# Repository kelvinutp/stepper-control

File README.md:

# stepper controls

This repository will contain the file for controlling stepper motors using a Raspberry pi GPIO and TB6560 drivers

|program|function|
|---|---|
|[clk_signal.py](https://github.com/kelvinutp/stepper-control/blob/main/clock_signal.py)|Generates a constant frequency clock signal (square wave)|
|[only_motors_control.py](https://github.com/kelvinutp/stepper-control/blob/main/only_motors_control.py)|Allows for controlling individual Enable (start/stop) and Direction (changes direction) pin on driver|
|[auto_moving.py](https://github.com/kelvinutp/stepper-control/blob/main/auto_moving.py)|Makes a motor moves repeteadly in prestablished timed sequences|
|[variador.py](https://github.com/kelvinutp/stepper-control/blob/main/variaddor.py)|enables the stepmotor for a soft start and a soft stop by gradually increasing and decreaseing th efrequency|
|[class.py](https://github.com/kelvinutp/stepper-control/blob/main/class.py)|A programmed class that provides all the functionalities for controlling a stepmotor|
|[Django files](https://github.com/kelvinutp/stepper-control/tree/main/django%20files)|a Django project created for providing a sort of UI capable of doing almost everything that is done by code|

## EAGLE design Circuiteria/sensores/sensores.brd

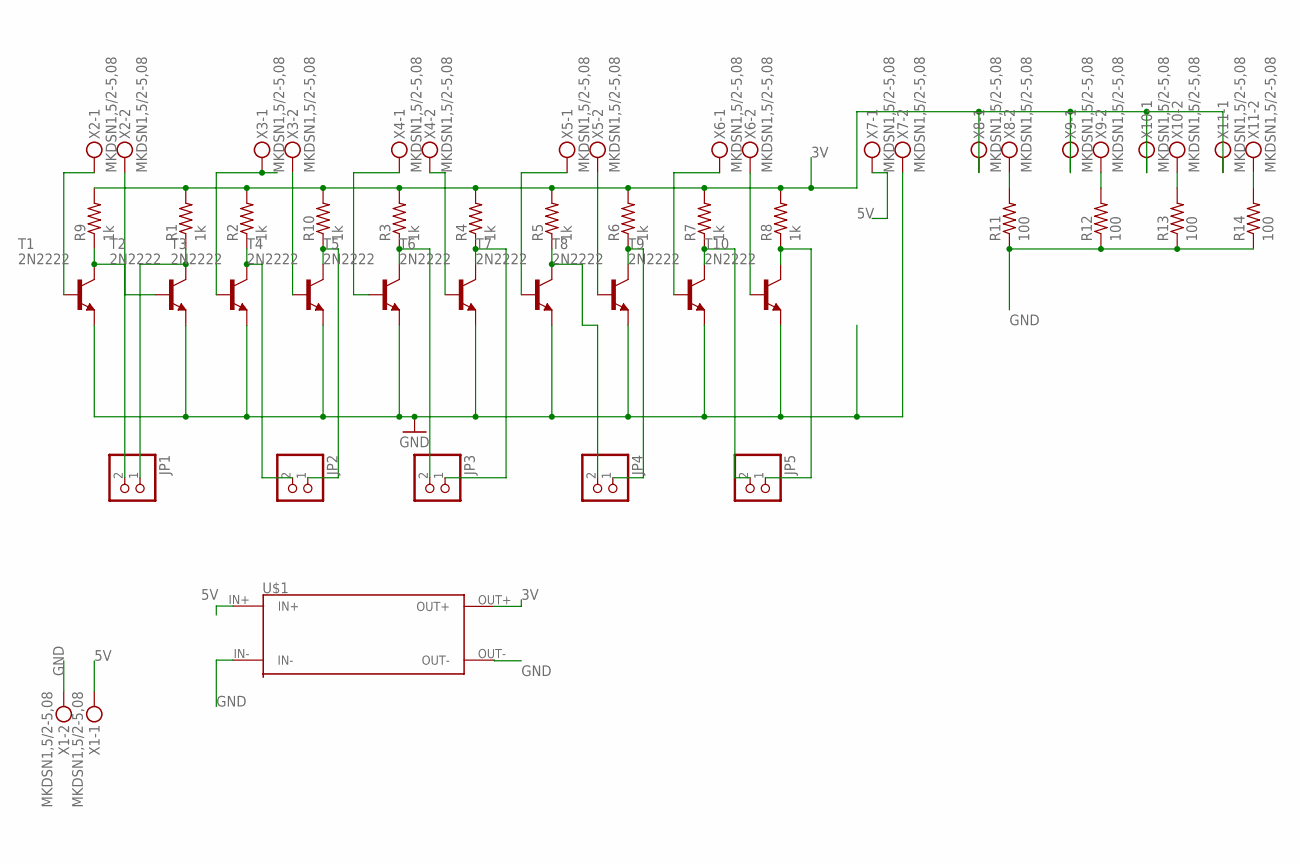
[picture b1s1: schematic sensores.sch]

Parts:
JP1, JP2, JP3, JP4, JP5: PINHD-1X2; 1X02
R1, R2, R3, R4, R5, R6, R7, R8, R9, R10: 1k; 0207/10
R11, R12, R13, R14: 100; 0207/10
T1, T2, T3, T4, T5, T6, T7, T8, T9, T10: 2N2222
U$1: LM2596
X1, X2, X3, X4, X5, X6, X7, X8, X9, X10, X11: MKDSN1,5/2-5,08

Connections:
3V: R1.2, R2.2, R3.2, R4.2, R5.2, R6.2, R7.2, R8.2, R9.2, R10.2, U$1.OUT+, X8.1, X9.1, X10.1, X11.1
5V: U$1.IN+, X1.1, X7.1
GND: R11.1, R12.1, R13.1, R14.1, T1.E, T2.E, T3.E, T4.E, T5.E, T6.E, T7.E, T8.E, T9.E, T10.E, U$1.IN-, U$1.OUT-, X1.2, X7.2
unnamed: T1.B, X2.1
unnamed: T4.B, X3.2
unnamed: T2.B, X2.2
unnamed: T3.B, X3.1
unnamed: T5.B, X4.1
unnamed: T6.B, X4.2
unnamed: T7.B, X5.1
unnamed: T8.B, X5.2
unnamed: T9.B, X6.1
unnamed: T10.B, X6.2
unnamed: JP3.1, R4.1, T6.C
unnamed: JP1.1, R1.1, T2.C
unnamed: JP2.2, R2.1, T3.C
unnamed: JP3.2, R3.1, T5.C
unnamed: JP4.2, R5.1, T7.C
unnamed: JP4.1, R6.1, T8.C
unnamed: JP5.2, R7.1, T9.C
unnamed: JP5.1, R8.1, T10.C
unnamed: JP1.2, R9.1, T1.C
unnamed: JP2.1, R10.1, T4.C
unnamed: R11.2, X8.2
unnamed: R12.2, X9.2
unnamed: R13.2, X10.2
unnamed: R14.2, X11.2

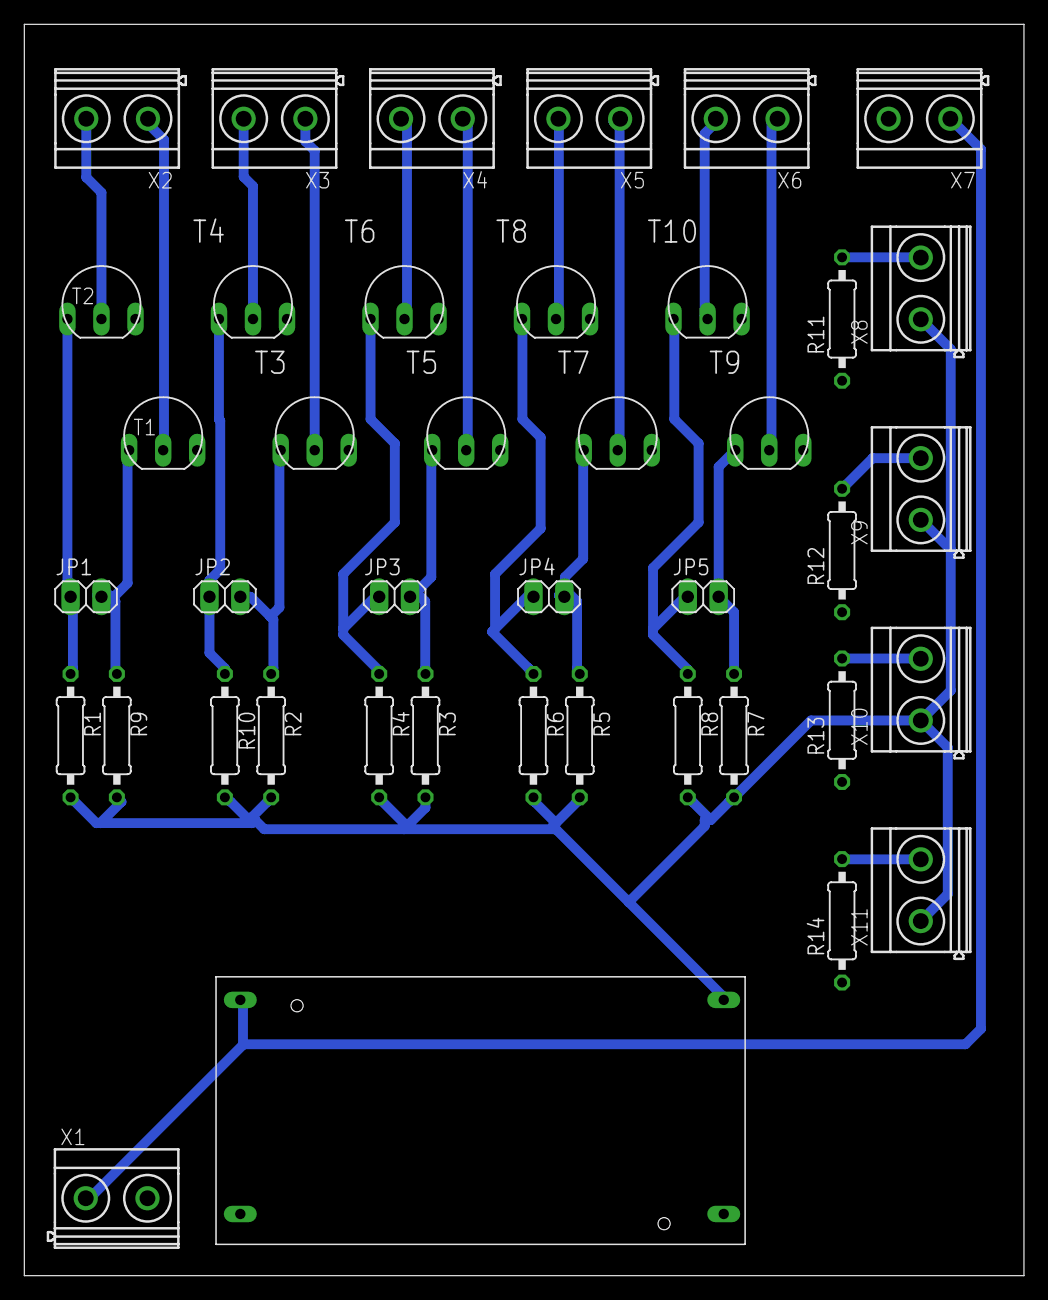
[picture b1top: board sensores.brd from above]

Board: 2 copper layers, 82.3 x 103.0 mm, 41 parts (0 on the bottom side), 27 nets.

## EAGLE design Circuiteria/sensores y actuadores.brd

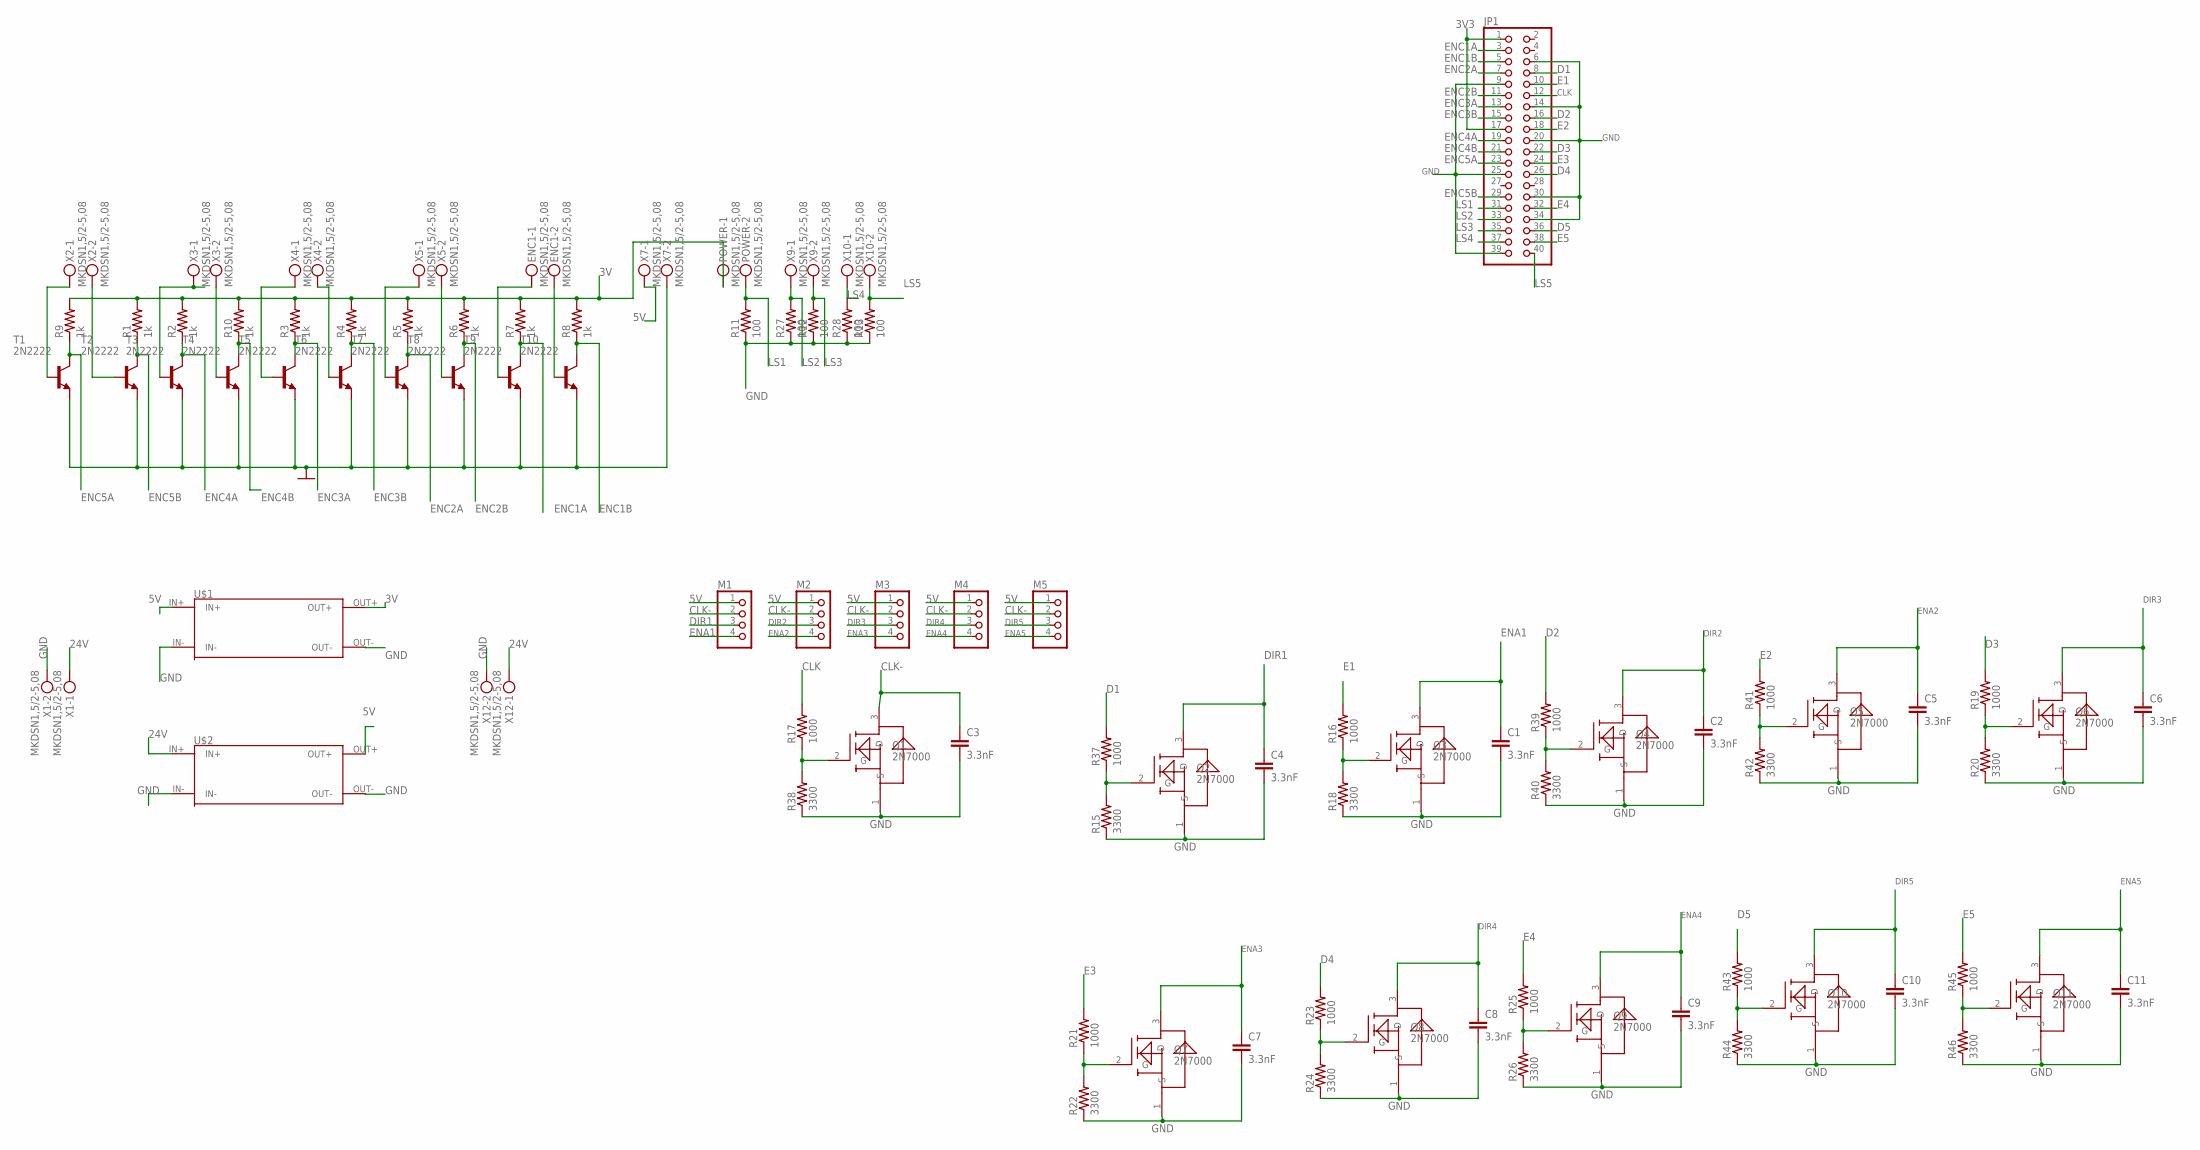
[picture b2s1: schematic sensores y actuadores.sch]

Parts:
C1, C2, C3, C4, C5, C6, C7, C8, C9, C10, C11: 3.3nF; C025-024X044
ENC1: MKDSN1,5/2-5,08
JP1: PINHD-2X20; 2X20
M1, M2, M3, M4, M5: PINHD-1X4; 1X04
POWER: MKDSN1,5/2-5,08
Q1, Q2, Q3, Q4, Q5, Q6, Q7, Q8, Q9, Q10, Q11: 2N7000
R1, R2, R3, R4, R5, R6, R7, R8, R9, R10: 1k; 0207/10
R11, R12, R13, R27, R28: 100; 0207/10
R15, R18, R20, R22, R24, R26, R38, R40, R42, R44, R46: 3300; 0207/10
R16, R17, R19, R21, R23, R25, R37, R39, R41, R43, R45: 1000; 0207/10
T1, T2, T3, T4, T5, T6, T7, T8, T9, T10: 2N2222
U$1, U$2: LM2596
X1, X2, X3, X4, X5, X7, X9, X10, X12: MKDSN1,5/2-5,08

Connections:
3V: POWER.1, R1.2, R2.2, R3.2, R4.2, R5.2, R6.2, R7.2, R8.2, R9.2, R10.2, U$1.OUT+
3V3: JP1.1, JP1.17
5V: M1.1, M2.1, M3.1, M4.1, M5.1, U$1.IN+, U$2.OUT+, X7.1
24V: U$2.IN+, X1.1, X12.1
CLK: JP1.12, R17.2
CLK-: C3.1, M1.2, M2.2, M3.2, M4.2, M5.2, Q1.3 (D)
D1: JP1.8, R37.2
D2: JP1.16, R39.2
D3: JP1.22, R19.2
D4: JP1.26, R23.2
D5: JP1.36, R43.2
DIR1: C4.1, M1.3, Q2.3 (D)
DIR2: C2.1, M2.3, Q4.3 (D)
DIR3: C6.1, M3.3, Q6.3 (D)
DIR4: C8.1, M4.3, Q8.3 (D)
DIR5: C10.1, M5.3, Q10.3 (D)
E1: JP1.10, R16.2
E2: JP1.18, R41.2
E3: JP1.24, R21.2
E4: JP1.32, R25.2
E5: JP1.38, R45.2
ENA1: C1.1, M1.4, Q3.3 (D)
ENA2: C5.1, M2.4, Q5.3 (D)
ENA3: C7.1, M3.4, Q7.3 (D)
ENA4: C9.1, M4.4, Q9.3 (D)
ENA5: C11.1, M5.4, Q11.3 (D)
ENC1A: JP1.3, R7.1, T9.C
ENC1B: JP1.5, R8.1, T10.C
ENC2A: JP1.7, R5.1, T7.C
ENC2B: JP1.11, R6.1, T8.C
ENC3A: JP1.13, R3.1, T5.C
ENC3B: JP1.15, R4.1, T6.C
ENC4A: JP1.19, R2.1, T3.C
ENC4B: JP1.21, R10.1, T4.C
ENC5A: JP1.23, R9.1, T1.C
ENC5B: JP1.29, R1.1, T2.C
GND: C1.2, C2.2, C3.2, C4.2, C5.2, C6.2, C7.2, C8.2, C9.2, C10.2, C11.2, JP1.6, JP1.9, JP1.14, JP1.20, JP1.25, JP1.30, JP1.34, JP1.39, Q1.1 (S), Q2.1 (S), Q3.1 (S), Q4.1 (S), Q5.1 (S), Q6.1 (S), Q7.1 (S), Q8.1 (S), Q9.1 (S), Q10.1 (S), Q11.1 (S), R11.1, R12.1, R13.1, R15.1, R18.1, R20.1, R22.1, R24.1, R26.1, R27.1, R28.1, R38.1, R40.1, R42.1, R44.1, R46.1, T1.E, T2.E, T3.E, T4.E, T5.E, T6.E, T7.E, T8.E, T9.E, T10.E, U$1.IN-, U$1.OUT-, U$2.IN-, U$2.OUT-, X1.2, X7.2, X12.2
LS1: JP1.31, POWER.2, R11.2
LS2: JP1.33, R27.2, X9.1
LS3: JP1.35, R12.2, X9.2
LS4: JP1.37, R28.2, X10.1
LS5: JP1.40, R13.2, X10.2
unnamed: T1.B, X2.1
unnamed: T4.B, X3.2
unnamed: T2.B, X2.2
unnamed: T3.B, X3.1
unnamed: T5.B, X4.1
unnamed: T6.B, X4.2
unnamed: T7.B, X5.1
unnamed: T8.B, X5.2
unnamed: ENC1.1, T9.B
unnamed: ENC1.2, T10.B
unnamed: Q1.2 (G), R17.1, R38.2
unnamed: Q2.2 (G), R15.2, R37.1
unnamed: Q3.2 (G), R16.1, R18.2
unnamed: Q4.2 (G), R39.1, R40.2
unnamed: Q5.2 (G), R41.1, R42.2
unnamed: Q6.2 (G), R19.1, R20.2
unnamed: Q7.2 (G), R21.1, R22.2
unnamed: Q8.2 (G), R23.1, R24.2
unnamed: Q9.2 (G), R25.1, R26.2
unnamed: Q10.2 (G), R43.1, R44.2
unnamed: Q11.2 (G), R45.1, R46.2

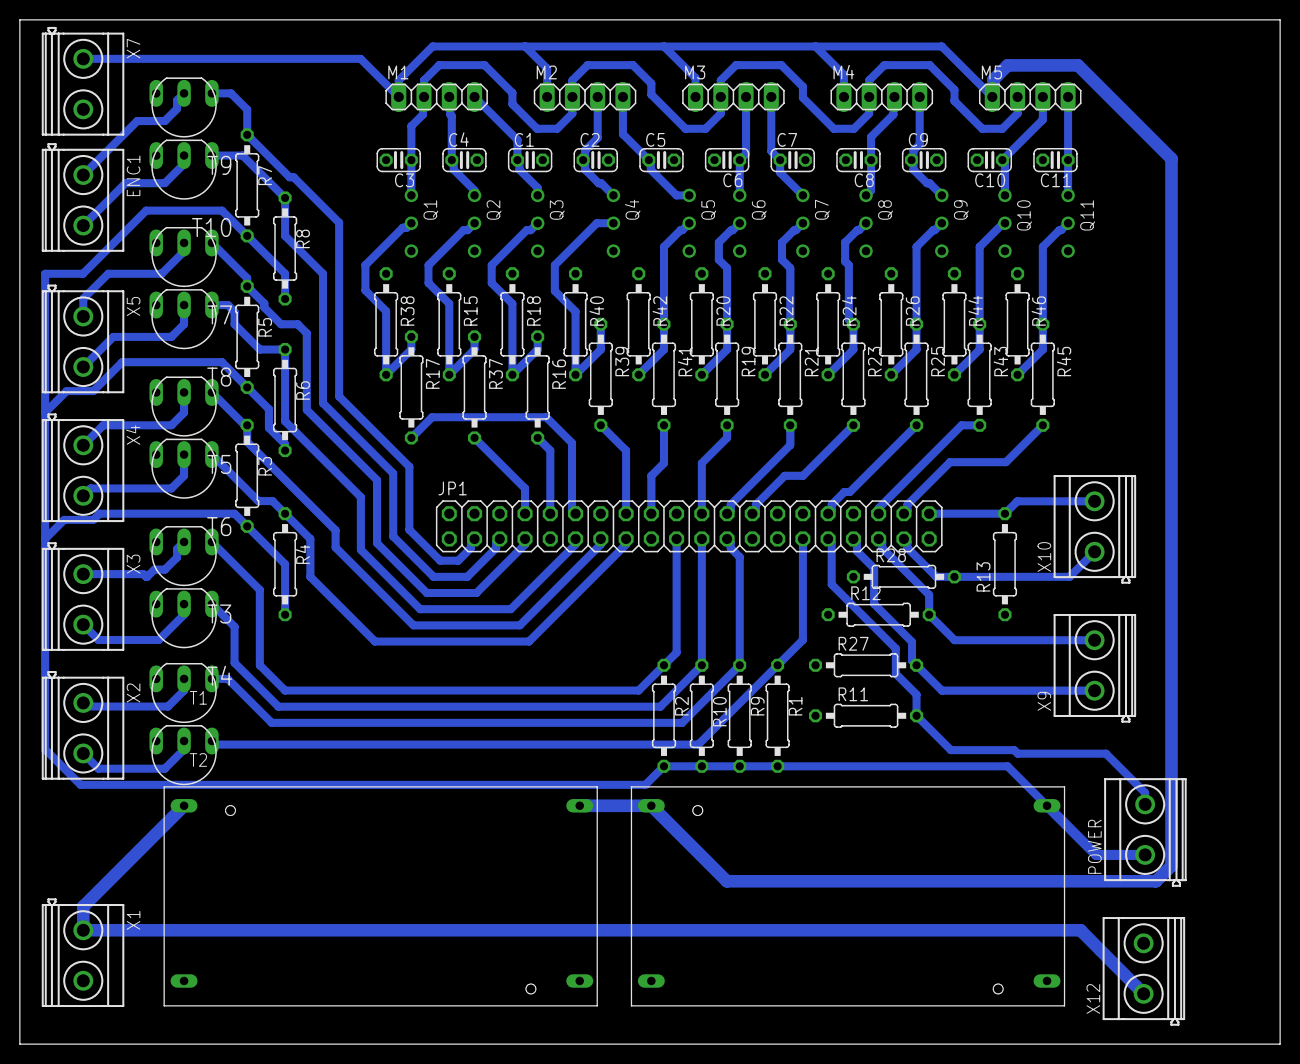
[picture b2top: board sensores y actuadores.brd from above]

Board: 2 copper layers, 126.7 x 103.0 mm, 88 parts (0 on the bottom side), 63 nets.

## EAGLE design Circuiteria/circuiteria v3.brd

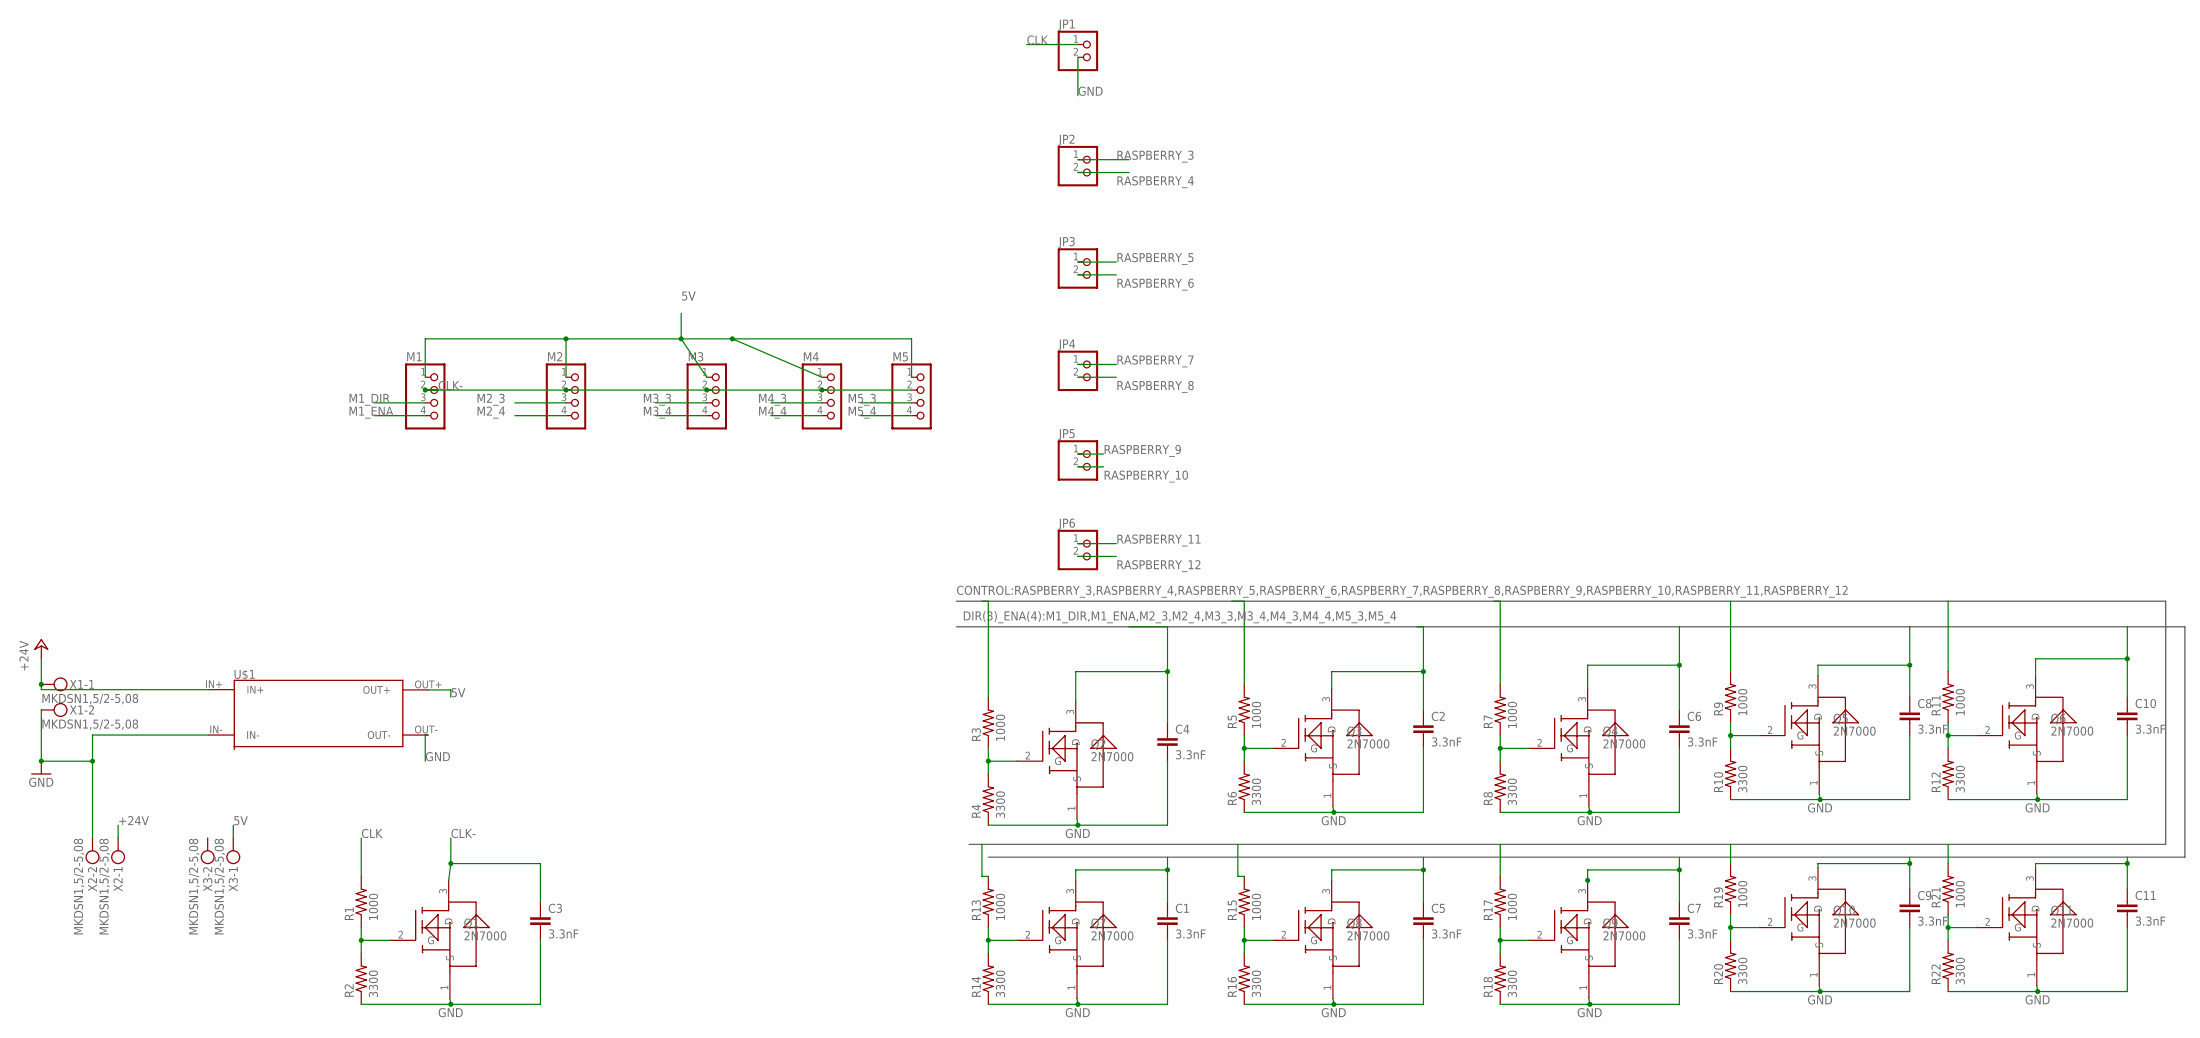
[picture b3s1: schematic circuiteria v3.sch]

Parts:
C1, C2, C3, C4, C5, C6, C7, C8, C9, C10, C11: 3.3nF; C025-024X044
JP1, JP2, JP3, JP4, JP5, JP6: PINHD-1X2; 1X02
M1, M2, M3, M4, M5: PINHD-1X4; 1X04
Q1, Q2, Q3, Q4, Q5, Q6, Q7, Q8, Q9, Q10, Q11: 2N7000
R1, R3, R5, R7, R9, R11, R13, R15, R17, R19, R21: 1000; 0411/15
R2, R4, R6, R8, R10, R12, R14, R16, R18, R20, R22: 3300; 0411/15
U$1: LM2596
X1, X2, X3: MKDSN1,5/2-5,08

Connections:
5V: M1.1, M2.1, M3.1, M4.1, M5.1, U$1.OUT+, X3.1
+24V: U$1.IN+, X1.1, X2.1
CLK: JP1.1, R1.2
CLK-: C3.1, M1.2, M2.2, M3.2, M4.2, M5.2, Q1.3 (D)
GND: C1.2, C2.2, C3.2, C4.2, C5.2, C6.2, C7.2, C8.2, C9.2, C10.2, C11.2, JP1.2, Q1.1 (S), Q2.1 (S), Q3.1 (S), Q4.1 (S), Q5.1 (S), Q6.1 (S), Q7.1 (S), Q8.1 (S), Q9.1 (S), Q10.1 (S), Q11.1 (S), R2.1, R4.1, R6.1, R8.1, R10.1, R12.1, R14.1, R16.1, R18.1, R20.1, R22.1, U$1.IN-, U$1.OUT-, X1.2, X2.2
M1_DIR: C4.1, M1.3, Q2.3 (D)
M1_ENA: C2.1, M1.4, Q3.3 (D)
M2_3: C6.1, M2.3, Q4.3 (D)
M2_4: C8.1, M2.4, Q5.3 (D)
M3_3: C10.1, M3.3, Q6.3 (D)
M3_4: C1.1, M3.4, Q7.3 (D)
M4_3: C5.1, M4.3, Q8.3 (D)
M4_4: C7.1, M4.4, Q9.3 (D)
M5_3: C9.1, M5.3, Q10.3 (D)
M5_4: C11.1, M5.4, Q11.3 (D)
unnamed: Q1.2 (G), R1.1, R2.2
unnamed: Q2.2 (G), R3.1, R4.2
unnamed: Q3.2 (G), R5.1, R6.2
unnamed: Q4.2 (G), R7.1, R8.2
unnamed: Q5.2 (G), R9.1, R10.2
unnamed: Q6.2 (G), R11.1, R12.2
unnamed: Q7.2 (G), R13.1, R14.2
unnamed: Q8.2 (G), R15.1, R16.2
unnamed: Q9.2 (G), R17.1, R18.2
unnamed: Q10.2 (G), R19.1, R20.2
unnamed: Q11.2 (G), R21.1, R22.2
RASPBERRY_3: JP2.1, R3.2
RASPBERRY_4: JP2.2, R5.2
RASPBERRY_5: JP3.1, R7.2
RASPBERRY_6: JP3.2, R9.2
RASPBERRY_7: JP4.1, R11.2
RASPBERRY_8: JP4.2, R13.2
RASPBERRY_9: JP5.1, R15.2
RASPBERRY_10: JP5.2, R17.2
RASPBERRY_11: JP6.1, R19.2
RASPBERRY_12: JP6.2, R21.2

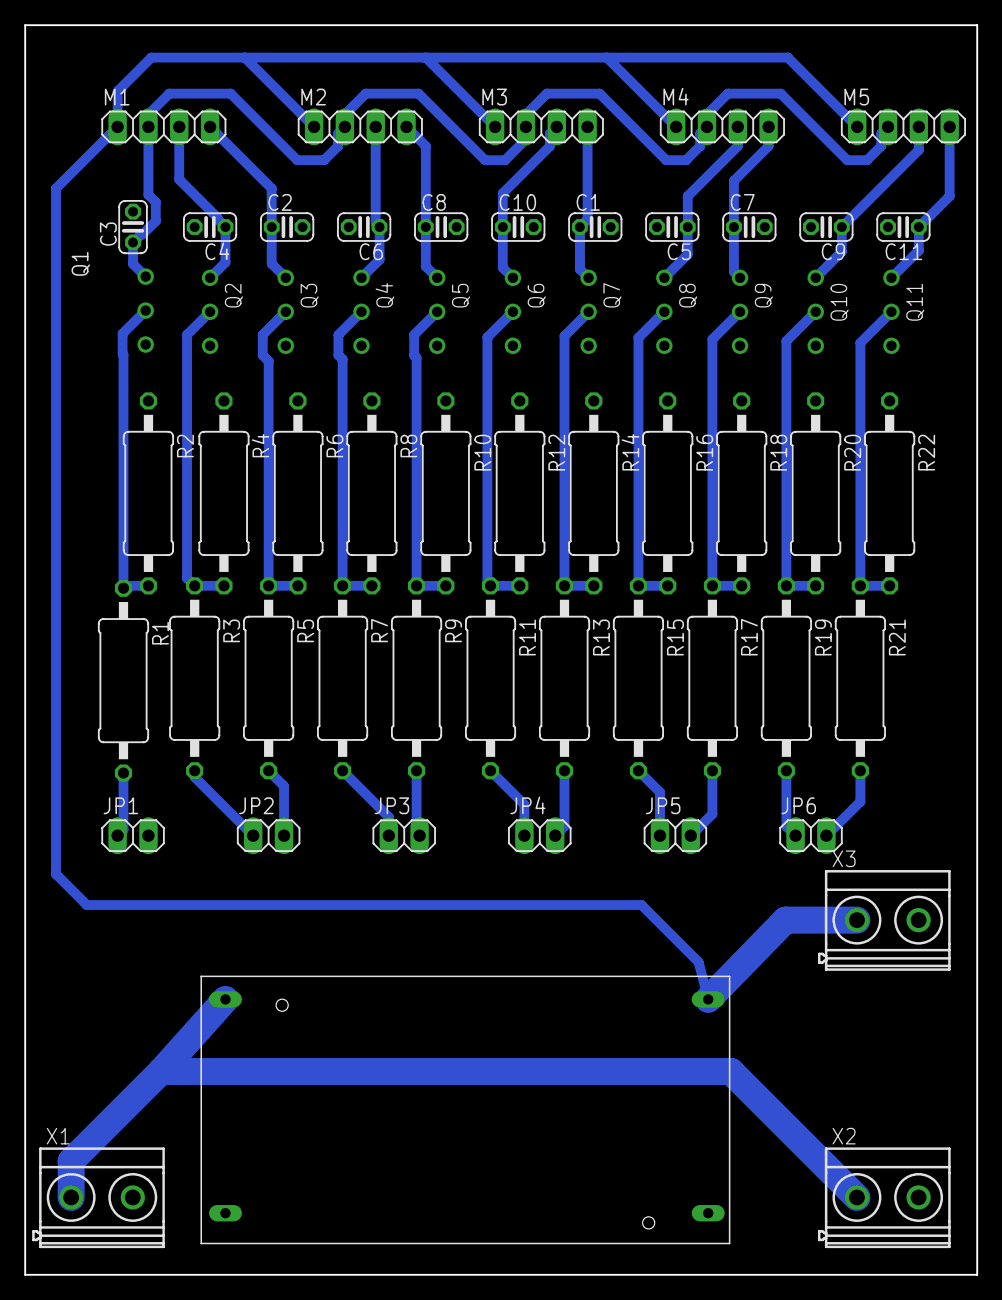
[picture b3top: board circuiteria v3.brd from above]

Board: 2 copper layers, 78.5 x 103.0 mm, 59 parts (0 on the bottom side), 36 nets.
